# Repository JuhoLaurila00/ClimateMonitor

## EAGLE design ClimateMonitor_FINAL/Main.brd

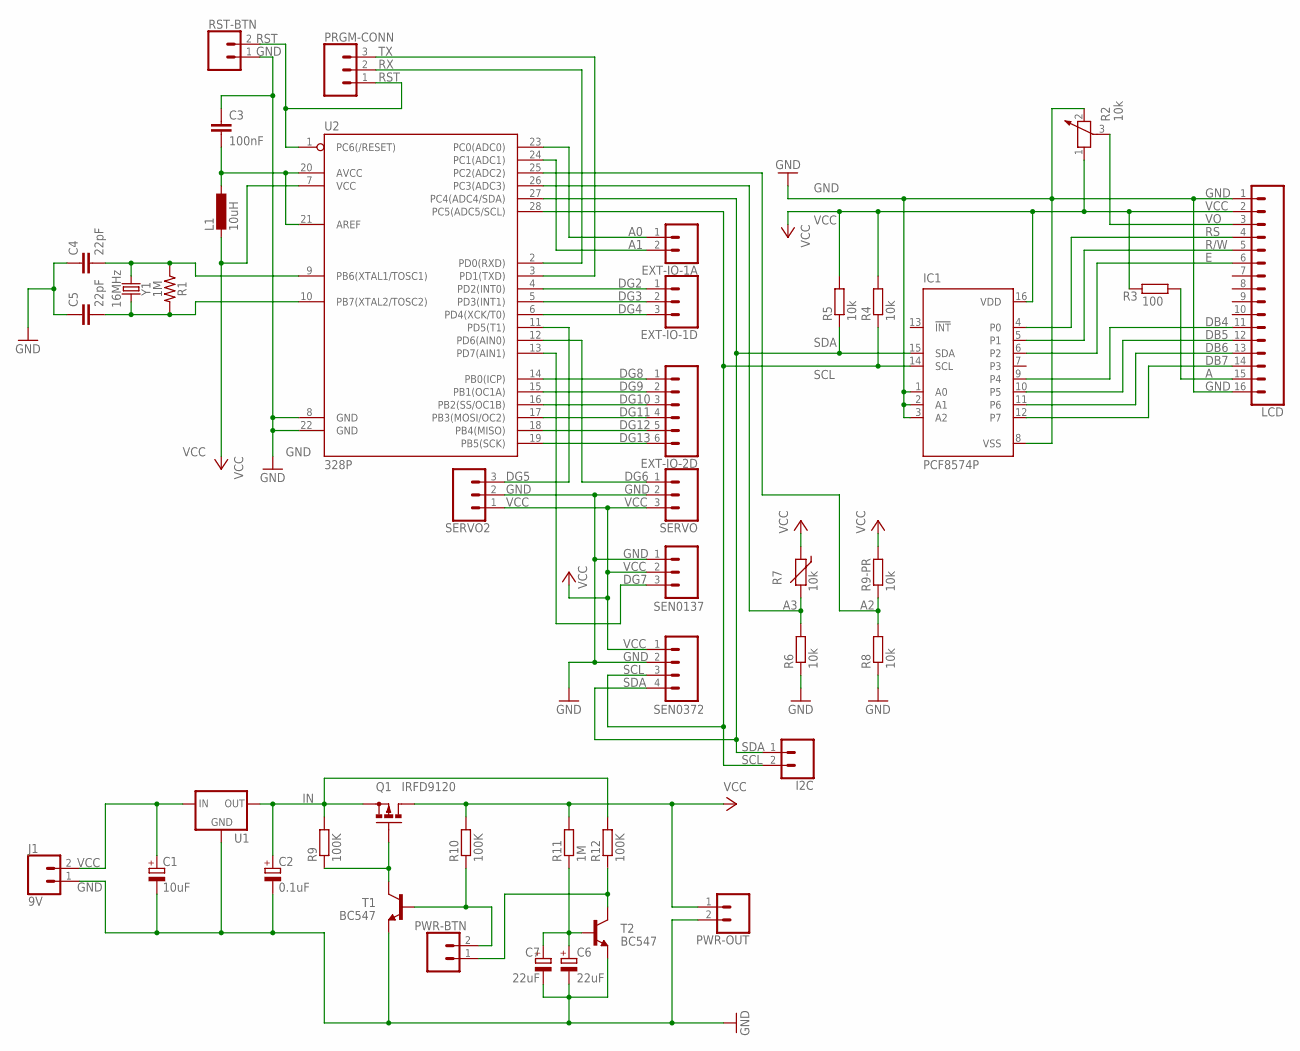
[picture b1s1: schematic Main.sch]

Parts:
C1: 10uF; E2,5-5
C2: 0.1uF; E2-4
C3: 100nF; C050-025X075
C4, C5: 22pF; CAP-PTH-2.54
C6, C7: 22uF; E2-5
EXT-IO-1A: CONN_02LOCK_LONGPADS; 1X02_LOCK_LONGPADS
EXT-IO-1D: CONN_03LONGPADS; 1X03_LONGPADS
EXT-IO-2D: CONN_06LONGPADS; 1X06_LONGPADS
I2C: CONN_02LOCK_LONGPADS; 1X02_LOCK_LONGPADS
IC1: PCF8574P; DIL16
J1: 9V; 1X02_LOCK_LONGPADS
L1: 10uH; 0204/5
LCD: CONN_16LONGPADS; 1X16_LONGPADS
PRGM-CONN: CONN_03LONGPADS; 1X03_LONGPADS
PWR-BTN: CONN_02LOCK_LONGPADS; 1X02_LOCK_LONGPADS
PWR-OUT: CONN_02LOCK_LONGPADS; 1X02_LOCK_LONGPADS
Q1: IRFD9120; C370-01
R1: 1M; AXIAL-0.3
R2: 10k; PT-10
R3: 100; 0207/10
R4, R5, R6, R8: 10k; 0207/10
R7: 10k; RS-2,5
R9, R10, R12: 100K; 0207/10
R9-PR: 10k; 0204V
R11: 1M; 0207/10
RST-BTN: CONN_02LOCK_LONGPADS; 1X02_LOCK_LONGPADS
SEN0137: CONN_03LONGPADS; 1X03_LONGPADS
SEN0372: CONN_04LONGPADS; 1X04_LONGPADS
SERVO, SERVO2: CONN_03LONGPADS; 1X03_LONGPADS
T1, T2: BC547; TO92
U1: V_REG_78XX-TO-220; TO-220-ALT
U2: 328P; DIP28
Y1: 16MHz; HC49US

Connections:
A: LCD.15, R3.2
A0: EXT-IO-1A.1, U2.23 (PC0(ADC0))
A1: EXT-IO-1A.2, U2.24 (PC1(ADC1))
A2: R8.2, R9-PR.1, U2.25 (PC2(ADC2))
A3: R6.2, R7.2, U2.26 (PC3(ADC3))
DB4: IC1.9 (P4), LCD.11
DB5: IC1.10 (P5), LCD.12
DB6: IC1.11 (P6), LCD.13
DB7: IC1.12 (P7), LCD.14
DG2: EXT-IO-1D.1, U2.4 (PD2(INT0))
DG3: EXT-IO-1D.2, U2.5 (PD3(INT1))
DG4: EXT-IO-1D.3, U2.6 (PD4(XCK/T0))
DG5: SERVO2.3, U2.11 (PD5(T1))
DG6: SERVO.1, U2.12 (PD6(AIN0))
DG7: SEN0137.3, U2.13 (PD7(AIN1))
DG8: EXT-IO-2D.1, U2.14 (PB0(ICP))
DG9: EXT-IO-2D.2, U2.15 (PB1(OC1A))
DG10: EXT-IO-2D.3, U2.16 (PB2(SS/OC1B))
DG11: EXT-IO-2D.4, U2.17 (PB3(MOSI/OC2))
DG12: EXT-IO-2D.5, U2.18 (PB4(MISO))
DG13: EXT-IO-2D.6, U2.19 (PB5(SCK))
E: IC1.6 (P2), LCD.6
GND: C1.-, C2.-, C3.1, C4.1, C5.1, C6.-, C7.-, IC1.1 (A0), IC1.2 (A1), IC1.3 (A2), IC1.8 (VSS), J1.1, LCD.1, LCD.16, PWR-OUT.2, R2.2, R6.1, R8.1, RST-BTN.1, SEN0137.1, SEN0372.2, SERVO.2, SERVO2.2, T1.1 (E), T2.1 (E), U1.GND, U2.8 (GND), U2.22 (GND)
IN: C2.+, Q1.S, R9.2, R12.2, U1.OUT
unnamed: Q1.G, R9.1, T1.3 (C)
unnamed: C3.2, L1.1, U2.20 (AVCC), U2.21 (AREF)
unnamed: C4.2, R1.P$1 (1), U2.9 (PB6(XTAL1/TOSC1)), Y1.1
unnamed: C5.2, R1.P$2 (2), U2.10 (PB7(XTAL2/TOSC2)), Y1.2
unnamed: PWR-BTN.2, R10.1, T1.2 (B)
unnamed: PWR-BTN.1, R12.1, T2.3 (C)
unnamed: C6.+, C7.+, R11.1, T2.2 (B)
R/W: IC1.5 (P1), LCD.5
RS: IC1.4 (P0), LCD.4
RST: PRGM-CONN.1, RST-BTN.2, U2.1 (PC6(/RESET))
RX: PRGM-CONN.2, U2.2 (PD0(RXD))
SCL: I2C.2, IC1.14 (SCL), R4.1, SEN0372.3, U2.28 (PC5(ADC5/SCL))
SDA: I2C.1, IC1.15 (SDA), R5.1, SEN0372.4, U2.27 (PC4(ADC4/SDA))
TX: PRGM-CONN.3, U2.3 (PD1(TXD))
VCC: C1.+, IC1.16 (VDD), J1.2, L1.2, LCD.2, PWR-OUT.1, Q1.D, Q1.D1 (D), R2.1, R3.1, R4.2, R5.2, R7.1, R9-PR.2, R10.2, R11.2, SEN0137.2, SEN0372.1, SERVO.3, SERVO2.1, U1.IN, U2.7 (VCC)
VO: LCD.3, R2.3

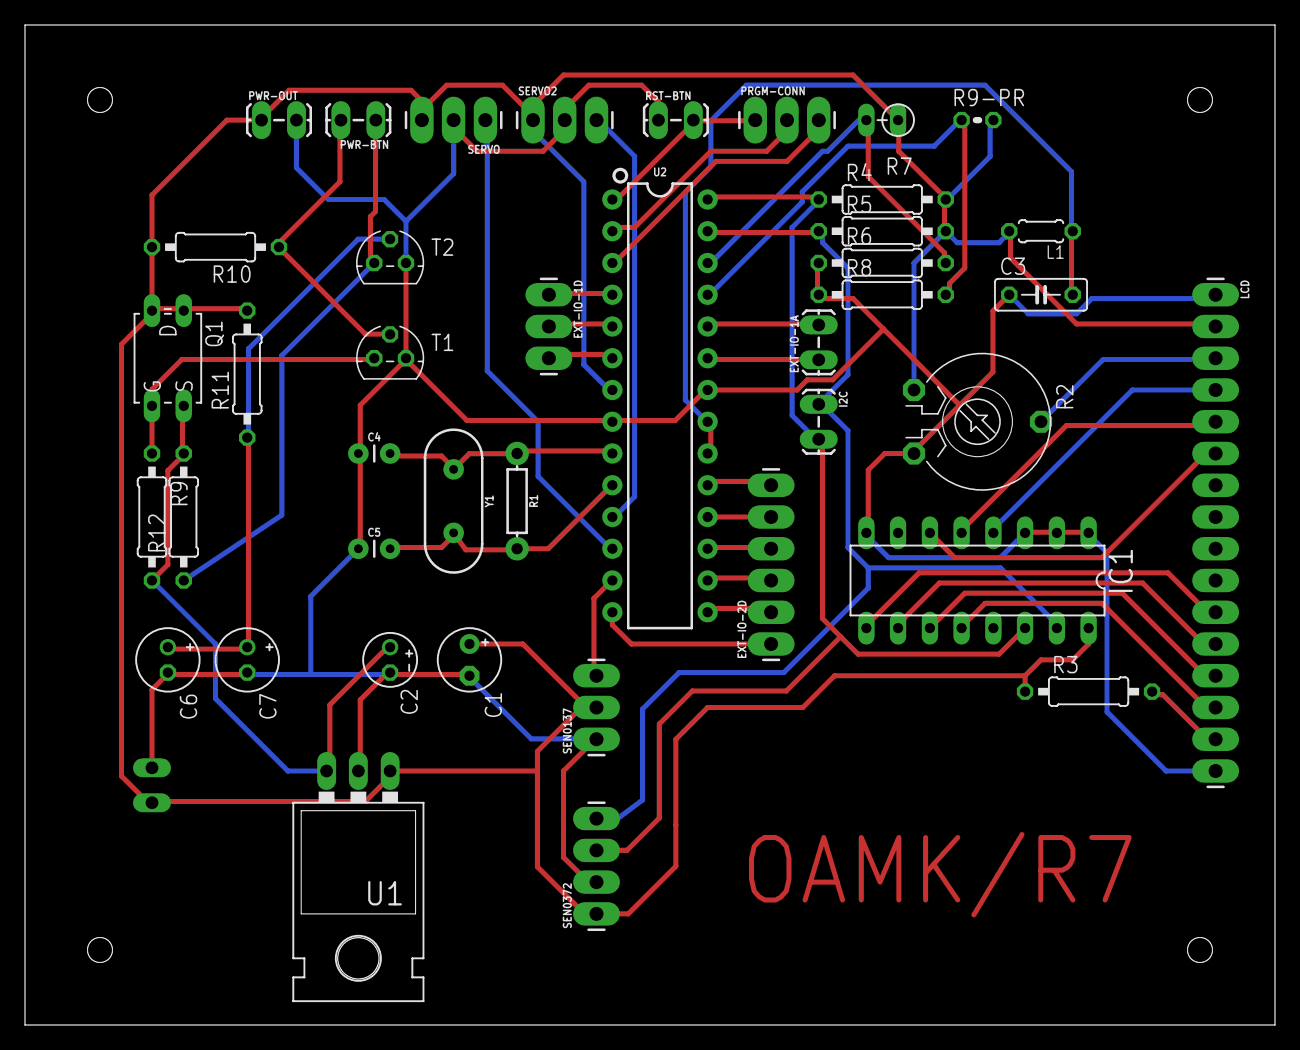
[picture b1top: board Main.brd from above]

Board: 2 copper layers, 100.0 x 80.0 mm, 42 parts (1 on the bottom side), 40 nets.

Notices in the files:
parts and their libraries:
SparkFun-Capacitors: Licensing: Creative Commons ShareAlike 4.0 International - https://creativecommons.org/licenses/by-sa/4.0
